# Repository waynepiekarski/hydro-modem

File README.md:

# HydroModem: Underwater Bell 103 modem implementation for low-power microcontrollers

Main project page: https://waynepiekarski.net/projects/hydro-modem.htm

HydroModem is a Bell 103 modem implementation to decode data from an always-on underwater hydrophone.
Designed for low-power microcontrollers such as AVR ATmega328P, it can listen underwater long-term
and implement the reliable trigger for an acoustic release in ocean research sensor prototypes.

This is an implementation of a Bell 103 modem decoder for Arduino devices with
low-power microcontrollers such as ATmega328P. It uses a simple Goertzel algorithm
to detect the power of two frequencies, compares them to determine mark-space bits,
and then decodes these into 8-bit characters. This method can handle background noise
and is used here to implement an acoustic underwater data transmit/receive mechanism.
Low-power devices can be permanently placed underwater, listening for a wakeup message,
and then take some kind of action like burn a nichrome wire for an acoustic release.
It is expected that the modem will run on its own ATmega328P since there is no time remaining,
and a co-processor like another ATmega328P will listen to the decoded characters and take action.
HydroModem is an easy-to-use component that can be used for building low-cost devices to support
research in the world's oceans.

This implementation supports a 2600 Hz sample rate on an ATmega328P at 16 MHz. Transmission
is with sine wave tones at 1070 Hz and 1270 Hz. The sample rate must be at least double the highest frequency
(Nyquist theorem) and during testing at low signal strength some sample rates were found to be more reliable than
others due to aliasing. This implementation supports up to 3300 Hz, but beyond that requires a higher clock
rate on the microcontroller, possibly using something like an ESP32S3. The input is read
in via the Arduino ADC, which needs to be able to capture samples at the frequency required.

The ATmega328P must be run at 16 MHz for 2600 Hz sample rate, requires at least 4.0V for this clock speed according to the datasheet,
and will draw 7 mA current or 0.028 W power. This is 1-2 orders of magnitude better than a Raspberry Pi running Linux, and capable
of running for weeks/months on a battery underwater.

# Sample audio

Sample audio generated by the modem tests, with spectrogram of the FSK frequencies in use, click for video:<br>

# Arduino Uno 16MHz on Linux command-line
The modemrx.ino project can be built on the command-line and also loaded into the Arduino IDE on any supported platform.
```
# Download arduino-cli (run once)
./download-arduino-tools

# Download arduino libraries (run once)
./download-arduino-libs

# Build and upload the modemrx project via USB serial
make -C modemrx upload

# Read characters decoded from the modemrx project
make -C modemrx read
```

# Listen and record audio on Linux via Arduino ADC
The recordwav.ino project allows you to listen to or record the audio at the ADC, making debugging with Linux tools easier.

```
# Download arduino-cli (run once)
./download-arduino-tools

# Download arduino libraries (run once)
./download-arduino-libs

# Build and upload the recordwav project via USB serial to record from the ADC
make -C recordwav upload

# Save audio to disk for offline testing
./recordwav/save_arduino_piezo.sh

# Listen to live audio on speakers
./recordwav/live_arduino_piezo.sh
```

# Linux testing of modem

The modem code also builds on Linux with the ability to encode to and decode from WAV files.
Automated regression tests are provided to ensure that different sample rates all work after changes are made.
Tests also verify that HydroModem's Bell 103 encoding is compatible with MiniModem <a href="http://www.whence.com/minimodem/">http://www.whence.com/minimodem/</a> on Linux.

```
# Download Debian/Ubuntu dependencies (run once)
./linux-test/apt-get-deps

# Build Linux binaries
make -C linux-test

# Generate WAV files using test strings
./linux-test/bell103_goertzel_wav_encoder

# Decode WAV files and recover test strings
./linux-test/bell103_goertzel_wav_decoder

# Run test suite that verifies encoding and decoding at various sample rates.
make -C linux-test test
```

# KiCAD v5 schematics and PCB layouts

These designs need to be tested in water and frequencies tuned for best performance.
Full project files are provided, including .kicad_pcb files for fabrication at <a href="https://oshpark.com">oshpark.com</a>.

## kicad/release-modem-mosfet-atmega328p-piezo/

Combination design implementing both the modem and the release mechanism.
5V ATmega328P running at 16 MHz.
Connects to a piezo-based microphone and includes protection diodes and an OPA1641 op-amp based on the
<a href="https://www.instructables.com/The-Gladys-Hydrophone/">Gladys Hydrophone by DJJules</a>.
Implements a P-channel MOSFET that can switch high-current 30 amps briefly to burn a nichrome release wire under water.
Provides on-board MCP1792 regulator for 5V from a >= 6.2V battery.
Arduino Uno-compatible AVRISP6 connector for programming.

<a href="kicad/release-modem-mosfet-atmega328p-piezo/release-modem-mosfet-atmega328p-piezo-schematic.pdf?raw=1">Schematics PDF</a>

<a href="kicad/release-modem-mosfet-atmega328p-piezo/design.kicad_pcb?raw=1">kicad_pcb</a>

## kicad/release-modem-atmega328p/

5V ATmega328P running at 16 MHz. Requires regulated 5V provided by the other board.
Connects to a piezo-based microphone and includes protection diodes and an OPA1641 op-amp based on the
<a href="https://www.instructables.com/The-Gladys-Hydrophone/">Gladys Hydrophone by DJJules</a>.
Only runs the HydroModem implementation, was used for early testing and separate from the release mechanism.
Arduino Uno-compatible AVRISP6 connector for programming.

<a href="kicad/release-modem-atmega328p/release-modem-atmega328p-schematic.pdf?raw=1">Schematics PDF</a>

<a href="kicad/release-modem-atmega328p/design.kicad_pcb?raw=1">kicad_pcb</a>

## kicad/release-modem-atmega328p-linein/

This is a simplified PCB design that does not provide any amplification for a piezo.
It connects any microphone that has been amplified to line-in voltages (+/- 1V) and passes this through to the ADC.
Only runs the HydroModem implementation and no release mechanism.

<a href="kicad/release-modem-atmega328p-linein/release-modem-atmega328p-linein-schematic.pdf?raw=1">Schematics PDF</a>

<a href="kicad/release-modem-atmega328p-linein/design.kicad_pcb?raw=1">kicad_pcb</a>

## kicad/release-serial-i2c-atmega328p-switch/

3.3V ATmega328P running at 8 MHz. Implements a MOSFET that can switch high-current to burn a nichrome release wire.
Provides on-board MCP1792 regulators for 3.3V and 5V from a >= 6.2V battery. Arduino Uno-compatible AVRISP6 connector
for programming. Works with either of the standalone modem implementations above.

<a href="kicad/release-serial-i2c-atmega328p-switch/release-serial-i2c-atmega328p-switch-schematic.pdf?raw=1">Schematics PDF</a>

<a href="kicad/release-serial-i2c-atmega328p-switch/design.kicad_pcb?raw=1">kicad_pcb</a>

# Source code GPLv3 license

HydroModem: Underwater Bell 103 modem implementation for low-power microcontrollers

Copyright (C) 2024-2025 Wayne Piekarski wayne@tinmith.net

https://waynepiekarski.net/projects/hydro-modem.htm

This program is free software: you can redistribute it and/or modify
it under the terms of the GNU General Public License as published by
the Free Software Foundation, either version 3 of the License, or
(at your option) any later version.

This program is distributed in the hope that it will be useful,
but WITHOUT ANY WARRANTY; without even the implied warranty of
MERCHANTABILITY or FITNESS FOR A PARTICULAR PURPOSE.  See the
GNU General Public License for more details.

You should have received a copy of the GNU General Public License
along with this program.  If not, see <http://www.gnu.org/licenses/>.

# KiCAD Schematics and PCB license CERN-OHL-S v2

This source describes Open Hardware and is licensed under the CERN-OHL-S v2.

You may redistribute and modify this source and make products using it under
the terms of the CERN-OHL-S v2 (https://ohwr.org/cern_ohl_s_v2.txt).

This source is distributed WITHOUT ANY EXPRESS OR IMPLIED WARRANTY,
INCLUDING OF MERCHANTABILITY, SATISFACTORY QUALITY AND FITNESS FOR A
PARTICULAR PURPOSE. Please see the CERN-OHL-S v2 for applicable conditions.

Source location: https://www.waynepiekarski.net/projects/hydro-modem.htm

As per CERN-OHL-S v2 section 4, should You produce hardware based on this
source, You must where practicable maintain the Source Location visible
on the external case of the device or other products you make using this
source.

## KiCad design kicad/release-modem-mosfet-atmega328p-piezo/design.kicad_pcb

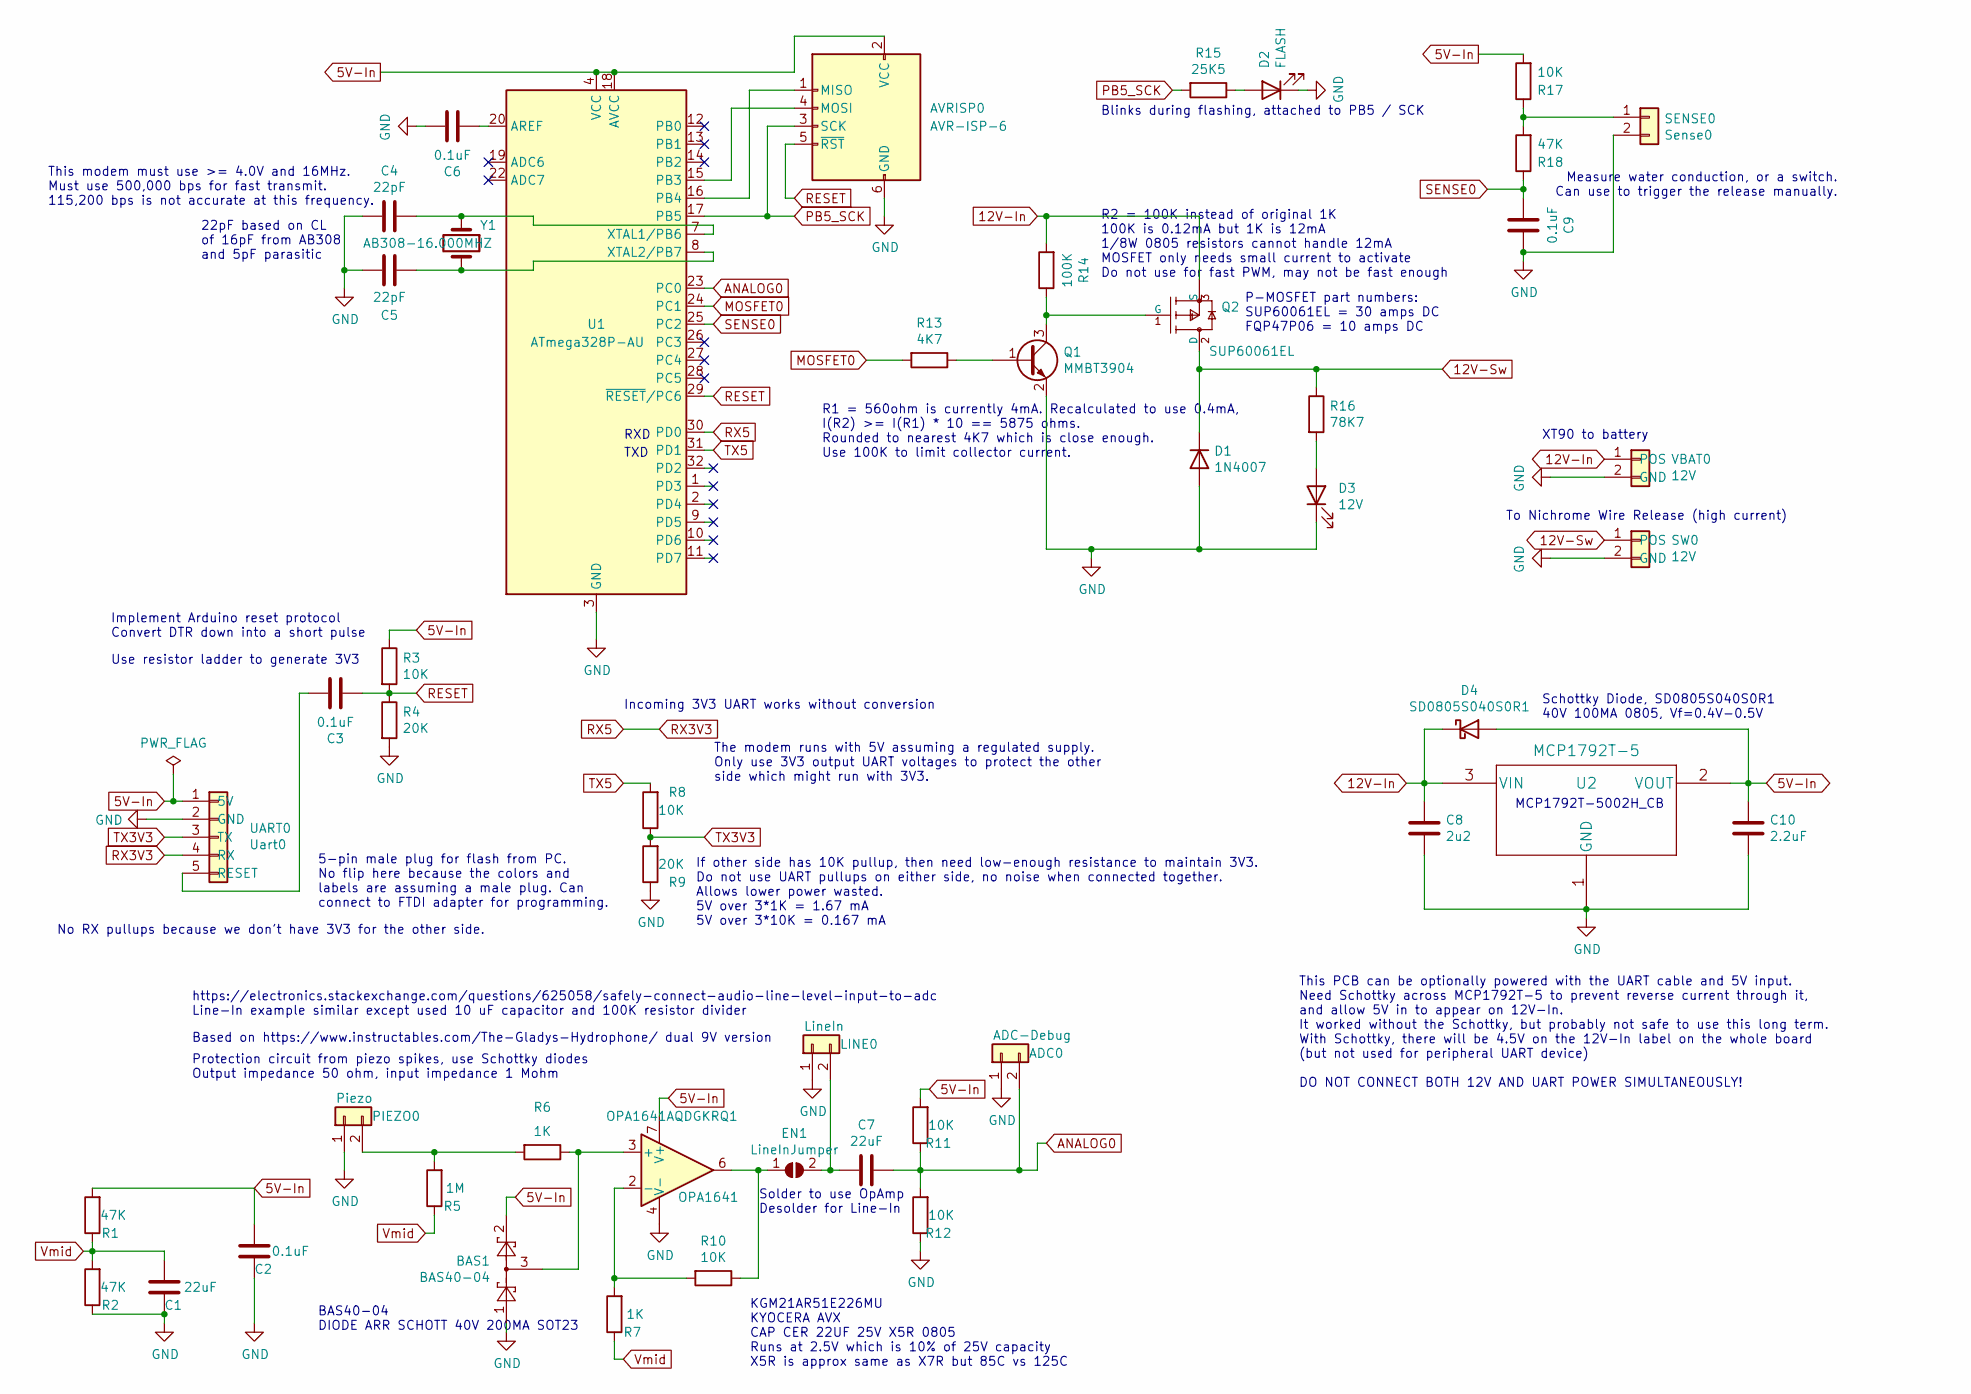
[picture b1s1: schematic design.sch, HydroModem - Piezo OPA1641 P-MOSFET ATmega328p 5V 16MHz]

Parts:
ADC0: ADC-Debug; WP_PinSocket_1x02_P2.54mm_Vertical
AVRISP0: AVR-ISP-6; PinHeader_2x03_P2.54mm_Vertical
BAS1: BAS40-04; SOT-23
C1, C7: 22uF; WP_C_0805_2012Metric_Pad1.15x1.40mm_HandSolder
C2, C3, C6, C9: 0.1uF; WP_C_0805_2012Metric_Pad1.15x1.40mm_HandSolder
C4, C5: 22pF; WP_C_0805_2012Metric_Pad1.15x1.40mm_HandSolder
C8: 2u2; WP_C_0805_2012Metric_Pad1.15x1.40mm_HandSolder; Part 08055C104KAT2A
C10: 2.2uF; WP_C_0805_2012Metric_Pad1.15x1.40mm_HandSolder; Part 08055C104KAT2A
D1: 1N4007; WP_D_SOD-123
D2: FLASH; WP_LED_0805_2012Metric_Pad1.15x1.40mm_HandSolder
D3: 12V; WP_LED_0805_2012Metric_Pad1.15x1.40mm_HandSolder
D4: SD0805S040S0R1; WP_LED_0805_2012Metric_Pad1.15x1.40mm_HandSolder
EN1: LineInJumper; SolderJumper-2_P1.3mm_Open_Pad1.0x1.5mm
LINE0: LineIn; WP_PinSocket_1x02_P2.54mm_Vertical
OPA1641: OPA1641AQDGKRQ1; VSSOP-8_3.0x3.0mm_P0.65mm
PIEZO0: Piezo; WP_PinSocket_1x02_P2.54mm_Vertical
Q1: MMBT3904; WP_SOT-23
Q2: SUP60061EL; WP_MOSFET_TO-220-3_Vertical; mouser part number 512-FQP47P06; digikey description MOSFET P-CH 60V 47A TO-220
R1, R2, R18: 47K; WP_R_0805_2012Metric_Pad1.15x1.40mm_HandSolder
R3, R8, R10, R11, R12, R17: 10K; WP_R_0805_2012Metric_Pad1.15x1.40mm_HandSolder
R4, R9: 20K; WP_R_0805_2012Metric_Pad1.15x1.40mm_HandSolder
R5: 1M; WP_R_0805_2012Metric_Pad1.15x1.40mm_HandSolder
R6, R7: 1K; WP_R_0805_2012Metric_Pad1.15x1.40mm_HandSolder
R13: 4K7; WP_R_0805_2012Metric_Pad1.15x1.40mm_HandSolder
R14: 100K; WP_R_0805_2012Metric_Pad1.15x1.40mm_HandSolder
R15: 25K5; WP_R_0805_2012Metric_Pad1.15x1.40mm_HandSolder
R16: 78K7; WP_R_0805_2012Metric_Pad1.15x1.40mm_HandSolder
SENSE0: Sense0; WP_Power_PinHeader_1x02_P2.54mm_Vertical
SW0: 12V; WP_TerminalBlock_16AWG_bornier-2_P5.08mm
U1: ATmega328P-AU; TQFP-32_7x7mm_P0.8mm
U2: MCP1792T-5; WP_SOT-23
UART0: Uart0; WP_Serial_5P_M
VBAT0: 12V; WP_TerminalBlock_16AWG_bornier-2_P5.08mm
Y1: AB308-16.000MHZ; Crystal_Round_D1.0mm_Vertical

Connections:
5V-In: AVRISP0.2 (VCC), BAS1.2, C2.2, C10.1, D4.2 (A), OPA1641.7 (V+), R1.2, R3.1, R11.2, R17.2, U1.4 (VCC), U1.6 (VCC), U1.18 (AVCC), U2.2 (VOUT), UART0.1 (5V)
12V-In: C8.1, D4.1 (K), Q2.3 (S), R14.2, U2.3 (VIN), VBAT0.1 (POS)
12V-Sw: D1.1 (K), Q2.2 (D), R16.1, SW0.1 (POS)
ANALOG0: ADC0.2, C7.1, R11.1, R12.2, U1.23 (PC0)
GND: ADC0.1, AVRISP0.6 (GND), BAS1.1, C1.1, C2.1, C4.2, C5.1, C6.1, C8.2, C9.1, C10.2, D1.2 (A), D2.1 (K), D3.1 (K), LINE0.1, OPA1641.4 (V-), PIEZO0.1, Q1.2 (E), R2.1, R4.2, R9.1, R12.1, SENSE0.2, SW0.2 (GND), U1.3 (GND), U1.5 (GND), U1.21 (GND), U2.1 (GND), UART0.2 (GND), VBAT0.2 (GND)
MOSFET0: R13.2, U1.24 (PC1)
unnamed: AVRISP0.1 (MISO), U1.16 (PB4)
unnamed: AVRISP0.4 (MOSI), U1.15 (PB3)
unnamed: BAS1.3, OPA1641.3 (+), R6.1
unnamed: C3.1, UART0.5 (RESET)
unnamed: C4.1, U1.7 (XTAL1/PB6), Y1.1
unnamed: C5.2, U1.8 (XTAL2/PB7), Y1.2
unnamed: C6.2, U1.20 (AREF)
unnamed: C7.2, EN1.2 (B), LINE0.2
unnamed: D2.2 (A), R15.1
unnamed: D3.2 (A), R16.2
unnamed: EN1.1 (A), OPA1641.6, R10.1
unnamed: OPA1641.2 (-), R7.2, R10.2
unnamed: PIEZO0.2, R5.2, R6.2
unnamed: Q1.1 (B), R13.1
unnamed: Q1.3 (C), Q2.1 (G), R14.1
unnamed: R17.1, R18.2, SENSE0.1
PB5_SCK: AVRISP0.3 (SCK), R15.2, U1.17 (PB5)
RESET: AVRISP0.5 (~RST), C3.2, R3.2, R4.1, U1.29 (~RESET~/PC6)
RX3V3: U1.30 (PD0), UART0.4 (RX)
SENSE0: C9.2, R18.1, U1.25 (PC2)
TX3V3: R8.1, R9.2, UART0.3 (TX)
TX5: R8.2, U1.31 (PD1)
Vmid: C1.2, R1.1, R2.2, R5.1, R7.1

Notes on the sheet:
RXD
TXD
Blinks during flashing, attached to PB5 / SCK
22pF based on CL of 16pF from AB308 and 5pF parasitic
This modem must use >= 4.0V and 16MHz. Must use 500,000 bps for fast transmit. 115,200 bps is not accurate at this frequency.
Implement Arduino reset protocol Convert DTR down into a short pulse
The modem runs with 5V assuming a regulated supply. Only use 3V3 output UART voltages to protect the other side which might run with 3V3.
If other side has 10K pullup, then need low-enough resistance to maintain 3V3. Do not use UART pullups on either side, no noise when connected together. Allows lower power wasted. 5V over 3*1K = 1.67 mA 5V over 3*10K = 0.167 mA
Incoming 3V3 UART works without conversion
No RX pullups because we don't have 3V3 for the other side.
Use resistor ladder to generate 3V3
Based on https://www.instructables.com/The-Gladys-Hydrophone/ dual 9V version
Protection circuit from piezo spikes, use Schottky diodes Output impedance 50 ohm, input impedance 1 Mohm
https://electronics.stackexchange.com/questions/625058/safely-connect-audio-line-level-input-to-adc Line-In example similar except used 10 uF capacitor and 100K resistor divider
KGM21AR51E226MU KYOCERA AVX CAP CER 22UF 25V X5R 0805 Runs at 2.5V which is 10% of 25V capacity X5R is approx same as X7R but 85C vs 125C
Solder to use OpAmp Desolder for Line-In
BAS40-04 DIODE ARR SCHOTT 40V 200MA SOT23
R2 = 100K instead of original 1K 100K is 0.12mA but 1K is 12mA 1/8W 0805 resistors cannot handle 12mA MOSFET only needs small current to activate Do not use for fast PWM, may not be fast enough
R1 = 560ohm is currently 4mA. Recalculated to use 0.4mA, I(R2) >= I(R1) * 10 == 5875 ohms. Rounded to nearest 4K7 which is close enough. Use 100K to limit collector current.
5-pin male plug for flash from PC. No flip here because the colors and labels are assuming a male plug. Can connect to FTDI adapter for programming.
Measure water conduction, or a switch. Can use to trigger the release manually.
XT90 to battery
MCP1792T-5002H_CB
Schottky Diode, SD0805S040S0R1 40V 100MA 0805, Vf=0.4V-0.5V
This PCB can be optionally powered with the UART cable and 5V input. Need Schottky across MCP1792T-5 to prevent reverse current through it, and allow 5V in to appear on 12V-In. It worked without the Schottky, but probably not safe to use this long term. With Schottky, there will be 4.5V on the 12V-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
To Nichrome Wire Release (high current)
P-MOSFET part numbers: SUP60061EL = 30 amps DC FQP47P06 = 10 amps DC

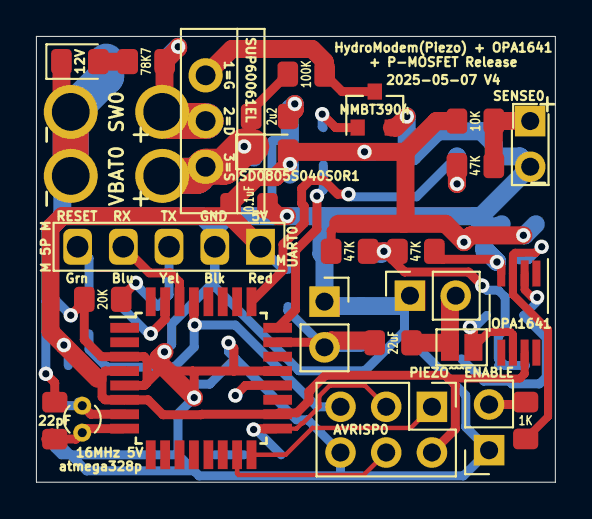
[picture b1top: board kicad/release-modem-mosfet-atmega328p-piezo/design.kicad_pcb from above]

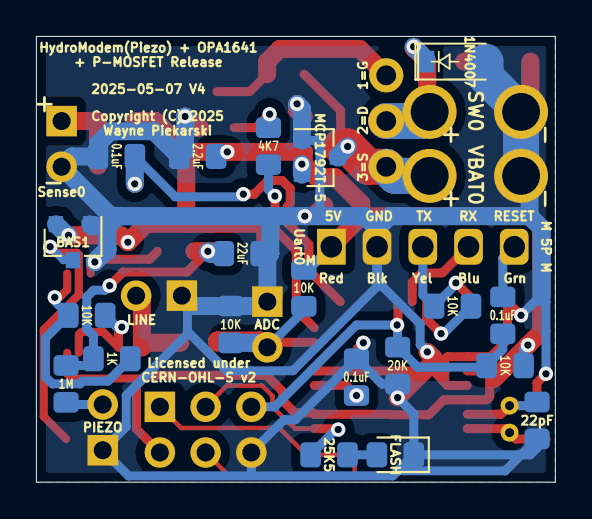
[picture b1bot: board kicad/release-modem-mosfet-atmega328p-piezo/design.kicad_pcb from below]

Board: 2 copper layers, 28.8 x 24.8 mm, 48 parts (20 on the bottom side), 29 nets.

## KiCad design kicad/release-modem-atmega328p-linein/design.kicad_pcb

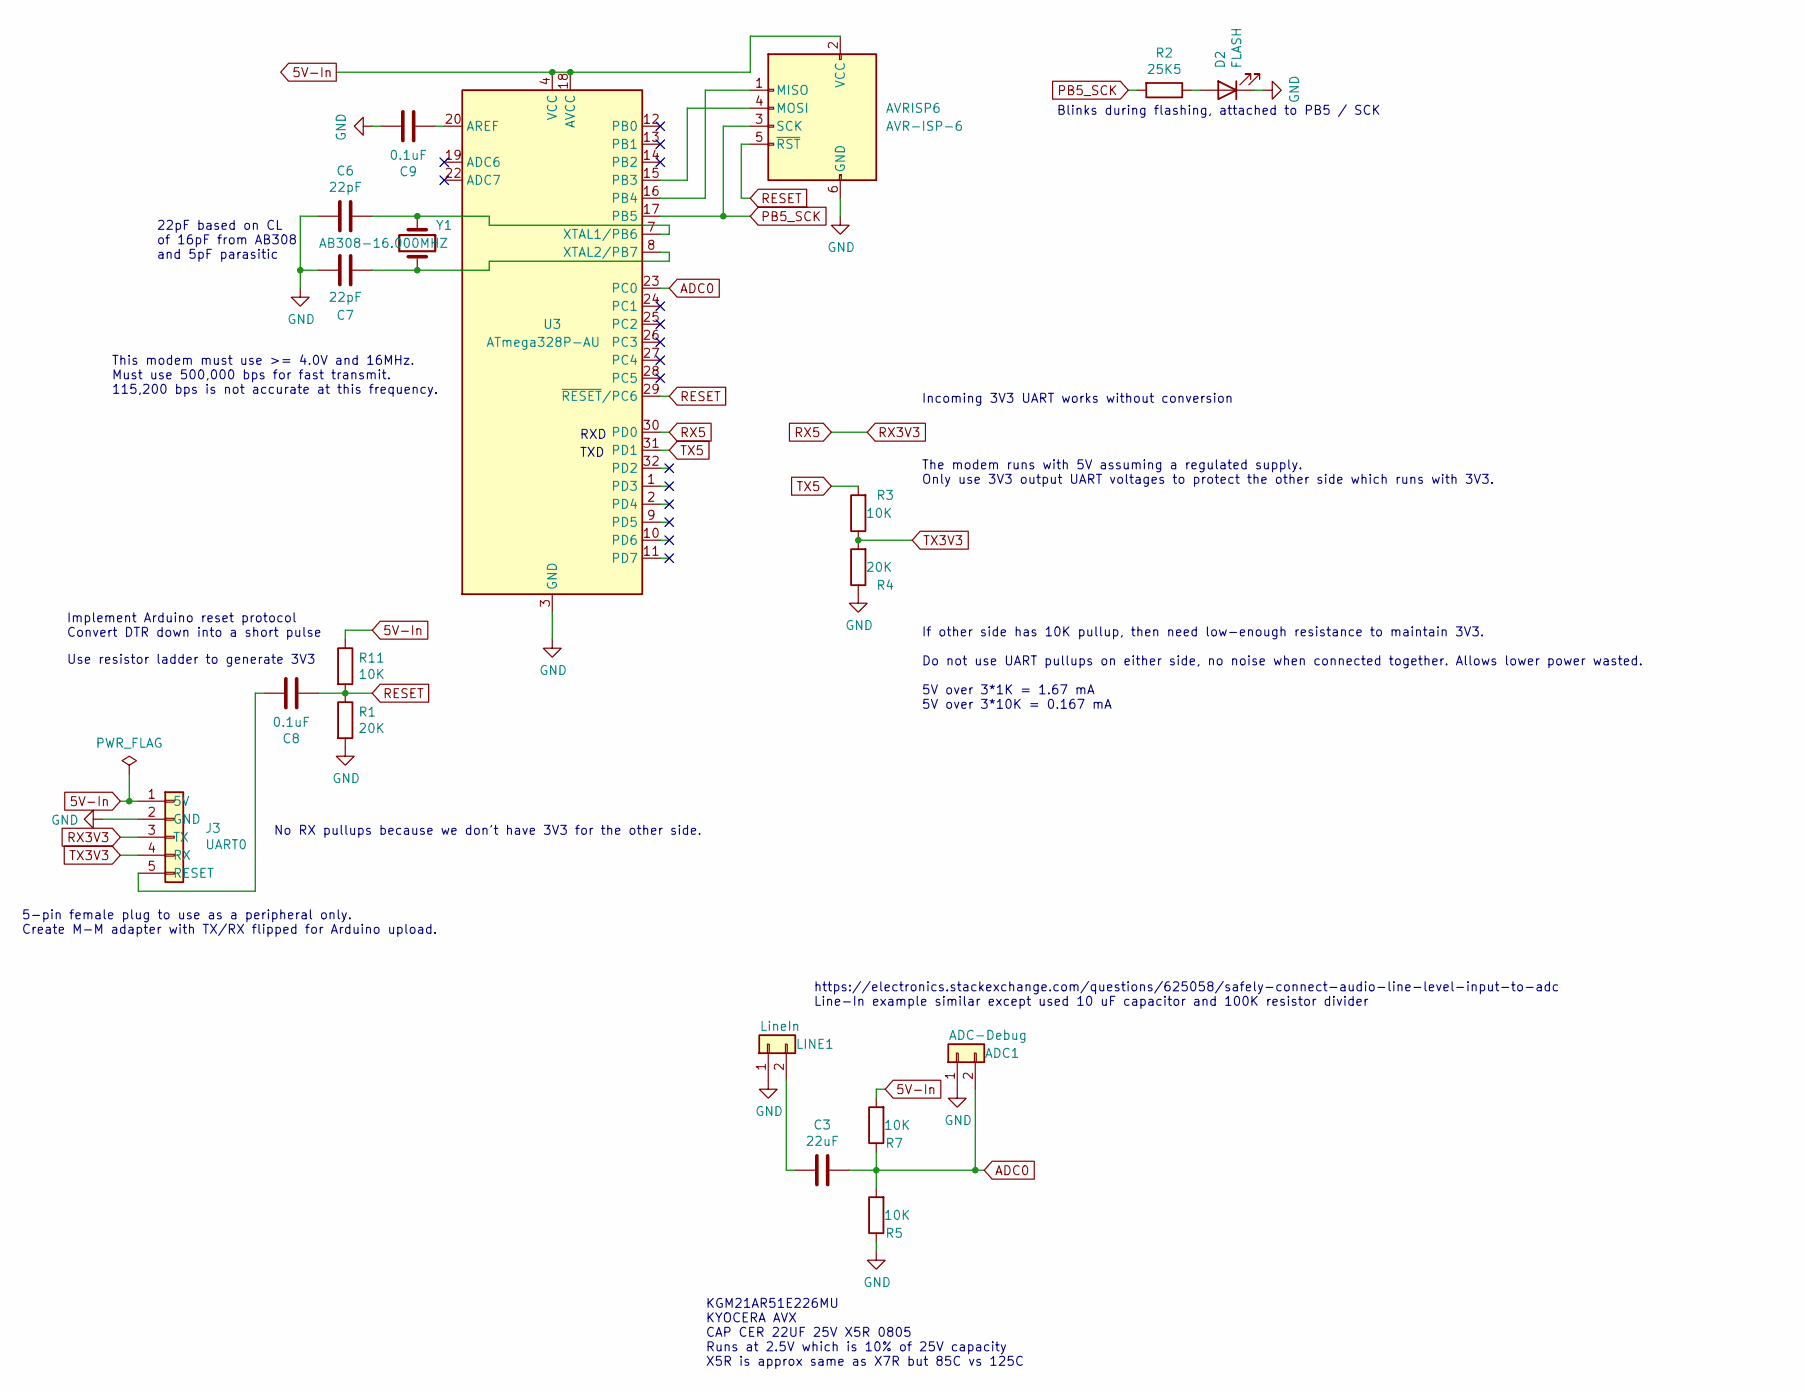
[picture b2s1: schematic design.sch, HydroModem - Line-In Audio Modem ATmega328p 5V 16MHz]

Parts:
ADC1: ADC-Debug; WP_PinSocket_1x02_P2.54mm_Vertical
AVRISP6: AVR-ISP-6; PinHeader_2x03_P2.54mm_Vertical
C3: 22uF; WP_C_0805_2012Metric_Pad1.15x1.40mm_HandSolder
C6, C7: 22pF; WP_C_0805_2012Metric_Pad1.15x1.40mm_HandSolder
C8, C9: 0.1uF; WP_C_0805_2012Metric_Pad1.15x1.40mm_HandSolder
D2: FLASH; WP_LED_0805_2012Metric_Pad1.15x1.40mm_HandSolder
J3: UART0; WP_Serial_5P_F
LINE1: LineIn; WP_PinSocket_1x02_P2.54mm_Vertical
R1, R4: 20K; WP_R_0805_2012Metric_Pad1.15x1.40mm_HandSolder
R2: 25K5; WP_R_0805_2012Metric_Pad1.15x1.40mm_HandSolder
R3, R5, R7, R11: 10K; WP_R_0805_2012Metric_Pad1.15x1.40mm_HandSolder
U3: ATmega328P-AU; TQFP-32_7x7mm_P0.8mm
Y1: AB308-16.000MHZ; Crystal_Round_D1.0mm_Vertical

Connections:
5V-In: AVRISP6.2 (VCC), J3.1 (5V), R7.2, R11.1, U3.4 (VCC), U3.6 (VCC), U3.18 (AVCC)
ADC0: ADC1.2, C3.1, R5.2, R7.1, U3.23 (PC0)
GND: ADC1.1, AVRISP6.6 (GND), C6.2, C7.1, C9.1, D2.1 (K), J3.2 (GND), LINE1.1, R1.2, R4.1, R5.1, U3.3 (GND), U3.5 (GND), U3.21 (GND)
unnamed: AVRISP6.1 (MISO), U3.16 (PB4)
unnamed: AVRISP6.4 (MOSI), U3.15 (PB3)
unnamed: C3.2, LINE1.2
unnamed: C6.1, U3.7 (XTAL1/PB6), Y1.1
unnamed: C7.2, U3.8 (XTAL2/PB7), Y1.2
unnamed: C8.1, J3.5 (RESET)
unnamed: C9.2, U3.20 (AREF)
unnamed: D2.2 (A), R2.1
PB5_SCK: AVRISP6.3 (SCK), R2.2, U3.17 (PB5)
RESET: AVRISP6.5 (~RST), C8.2, R1.1, R11.2, U3.29 (~RESET~/PC6)
RX3V3: J3.3 (TX), U3.30 (PD0)
TX3V3: J3.4 (RX), R3.1, R4.2
TX5: R3.2, U3.31 (PD1)

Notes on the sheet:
RXD
TXD
Blinks during flashing, attached to PB5 / SCK
22pF based on CL of 16pF from AB308 and 5pF parasitic
This modem must use >= 4.0V and 16MHz. Must use 500,000 bps for fast transmit. 115,200 bps is not accurate at this frequency.
Implement Arduino reset protocol Convert DTR down into a short pulse
The modem runs with 5V assuming a regulated supply. Only use 3V3 output UART voltages to protect the other side which runs with 3V3.
5-pin female plug to use as a peripheral only. Create M-M adapter with TX/RX flipped for Arduino upload.
If other side has 10K pullup, then need low-enough resistance to maintain 3V3. Do not use UART pullups on either side, no noise when connected together. Allows lower power wasted. 5V over 3*1K = 1.67 mA 5V over 3*10K = 0.167 mA
Incoming 3V3 UART works without conversion
No RX pullups because we don't have 3V3 for the other side.
Use resistor ladder to generate 3V3
https://electronics.stackexchange.com/questions/625058/safely-connect-audio-line-level-input-to-adc Line-In example similar except used 10 uF capacitor and 100K resistor divider
KGM21AR51E226MU KYOCERA AVX CAP CER 22UF 25V X5R 0805 Runs at 2.5V which is 10% of 25V capacity X5R is approx same as X7R but 85C vs 125C

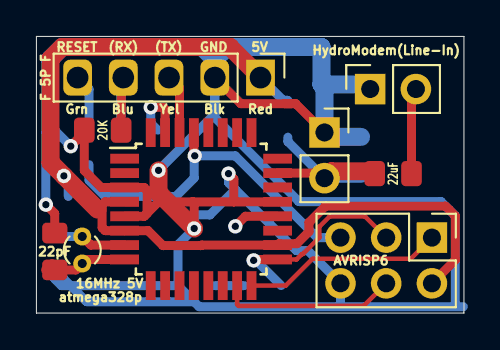
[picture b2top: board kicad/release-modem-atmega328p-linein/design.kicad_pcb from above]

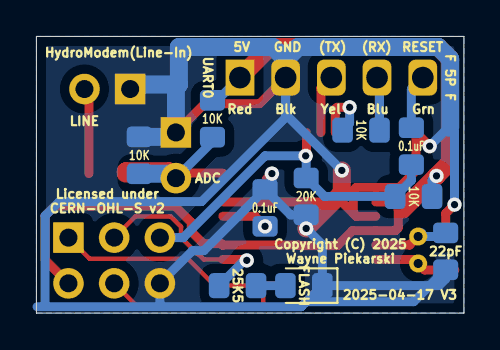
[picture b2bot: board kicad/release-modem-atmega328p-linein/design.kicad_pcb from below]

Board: 2 copper layers, 23.7 x 15.4 mm, 19 parts (10 on the bottom side), 16 nets.

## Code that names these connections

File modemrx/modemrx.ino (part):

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#endif // __AVR__

#ifdef __AVR__
#define PIN_STATUS_LED 13 // PB5, SCK, standard Arduino Uno LED, physical 17)
static_assert(PIN_STATUS_LED == LED_BUILTIN);

// Attach piezo microphone to analog pin 0 to read audio from the ADC (pin 14 = A0 = PC0 = physical 23)
#define ANALOG_PIN A0
static_assert(ANALOG_PIN == 14);
// Attach oscilloscope to digital pin 7 to see pulse at the start and end of interrupt handler (digital pin 7 = PD7 = physical 11)
#define SCOPE_PIN  7
// Second oscilloscope pin which toggles if a sample has taken too long (digital pin 6 = PD6 = physical 10)
#define ERROR_PIN  6
// Manual trigger of the release mechanism, short pin to ground (pin 16 = A2 = PC2 = physical 25)
#define PIN_TRIGGER A2
static_assert(PIN_TRIGGER == 16);
// MOSFET release (pin 15 = A1 = PC1 = physical 24)
#define PIN_MOSFET 15
static_assert(PIN_TRIGGER != PIN_MOSFET);
static_assert(PIN_TRIGGER != ANALOG_PIN);
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
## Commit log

2025-01-16 Initial repo
2025-01-27 Scripts to download Arduino libraries for AVR atmega328p support with arduino-cli
2025-01-27 Apply GPLv3 license to HydroModem repository
2025-01-27 Ignore generated build files and downloads
2025-02-06 HydroModem test implementation for Linux development
2025-02-06 Audio recorder for Arduino atmega328p with Linux client for recording and live monitoring
2025-02-06 HydroModem implementation for Arduino atmega328p and Makefile for arduino-cli
2025-02-06 Web-browser implementation of Bell103 encoder for HydroModem
2025-02-06 Sample spectrogram video and thumbnail generated by Linux tests
2025-02-06 Add README.md documentation for HydroModem
2025-02-07 Fix up README.md to match changes in https://waynepiekarski.net/projects/hydro-modem.htm
2025-03-19 Implement MOSFET-based release KiCAD schematic and PCB layout using 3.3V 8MHz atmega328p licensed under CERN-OHL-S v2
2025-03-19 Implement CERN-OHL-S v2 license and copyright to KiCAD schematic files
2025-03-19 Implement piezo modem KiCAD schematic and PCB layout using 5V 16MHz atmega328p licensed under CERN-OHL-S v2
2025-03-20 Render a preview of the PCB layout and schematics
2025-03-25 OpenSCAD model for a nichrome release mechanism licensed under CERN-OHL-S v2
2025-04-17 Clean up Arduino upload and bootloader installation in Makefiles
2025-04-17 Change to 500000 baud since 1000000 was unreliable
2025-04-17 Enable LED and implement debugging in the main loop
2025-04-17 Implement LED debugging and skip printing timeout warnings in graphical debug mode
2025-04-17 Scripts to play and record from the HydroModem PCB with piezo microphone
2025-04-17 Use grep --text otherwise the script fails when grep detects the input as a binary file
2025-04-17 Rework OpenSCAD nichrome release model to use square washers instead of nuts to fasten the wire
2025-04-17 Adjust AWG16 holes to 2.1mm as measured with tinned wires, AWG18 barely fit into these
2025-04-17 Rework the piezo input to use an OPA1641 opamp
2025-04-17 MOSFET release implementation for Arduino atmega328p and Makefile for arduino-cli
2025-04-17 Update PNG and PDF renderings based on recent KiCAD commits
2025-04-26 Add a simplified line-in voltage version of the release-modem-atmega328p PCB
2025-04-26 Update README to mention new OPA1641 and line-in PCB variants
2025-04-28 Add SUP60061EL-GE3 to schematic, supports 30 amps DC instead of 10 amps from FQP47P06
2025-05-09 Download arduino CLI tools for Intel 32-bit machines
2025-05-09 Clean up comments about the pin allocations
2025-05-09 Implement wake-word detector and MOSFET release in the modemrx implementation since there was CPU time available, used with release-modem-mosfet-atmega328p-piezo PCB
2025-05-09 Implement combined modem, wake-word detector, and MOSFET release in a single atmega328p PCB
2025-06-01 Script to build a Debian 12 bookworm debootstrap and verify apt-get dependencies are correct
2025-06-01 Add apt-get-deps script to download build dependencies
2025-06-01 Top-level Makefile to download dependencies and build all projects
2025-06-01 Remove unused .gitignore file
2025-06-07 Debian and Raspbian requires dialout to access /dev/ttyUSB* devices
2025-06-07 Fix Raspbian and non-x86-64 downloading of Arduino tools, only copy Wire patches if they are present
2025-06-07 Only enable the LED if a detected character matches the wake word, otherwise the LED is off
2025-07-23 Change OpenSCAD slicer symlink
2025-07-23 Add Nichrome 80 32AWG text label to the OpenSCAD release mechanism
2025-07-23 Modify --timing-drop to support integer argument for testing
2025-07-23 Implement --gen-subtitles in modem decoder and overlay these in ffmpeg generated videos
2025-07-25 Allow decoder to exit success if no text is decoded if there is no expected string
2025-07-25 Support output directory when generating spectrogram files

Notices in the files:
kicad/release-modem-atmega328p-linein/design.kicad_pcb:
Copyright (C) 2025
kicad/release-modem-atmega328p-linein/design.sch:
Copyright (C) Wayne Piekarski 2024-2025 - Licensed under CERN-OHL-S v2
